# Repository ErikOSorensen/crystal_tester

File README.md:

# Crystal tester
Creating pcbs for crystal tester (for measuring motional parameters for crystal filters).

- 2023-12-17: First G3UUR board populated.
- 2023-12-17: First crystals tested.

## The tester

## First tests

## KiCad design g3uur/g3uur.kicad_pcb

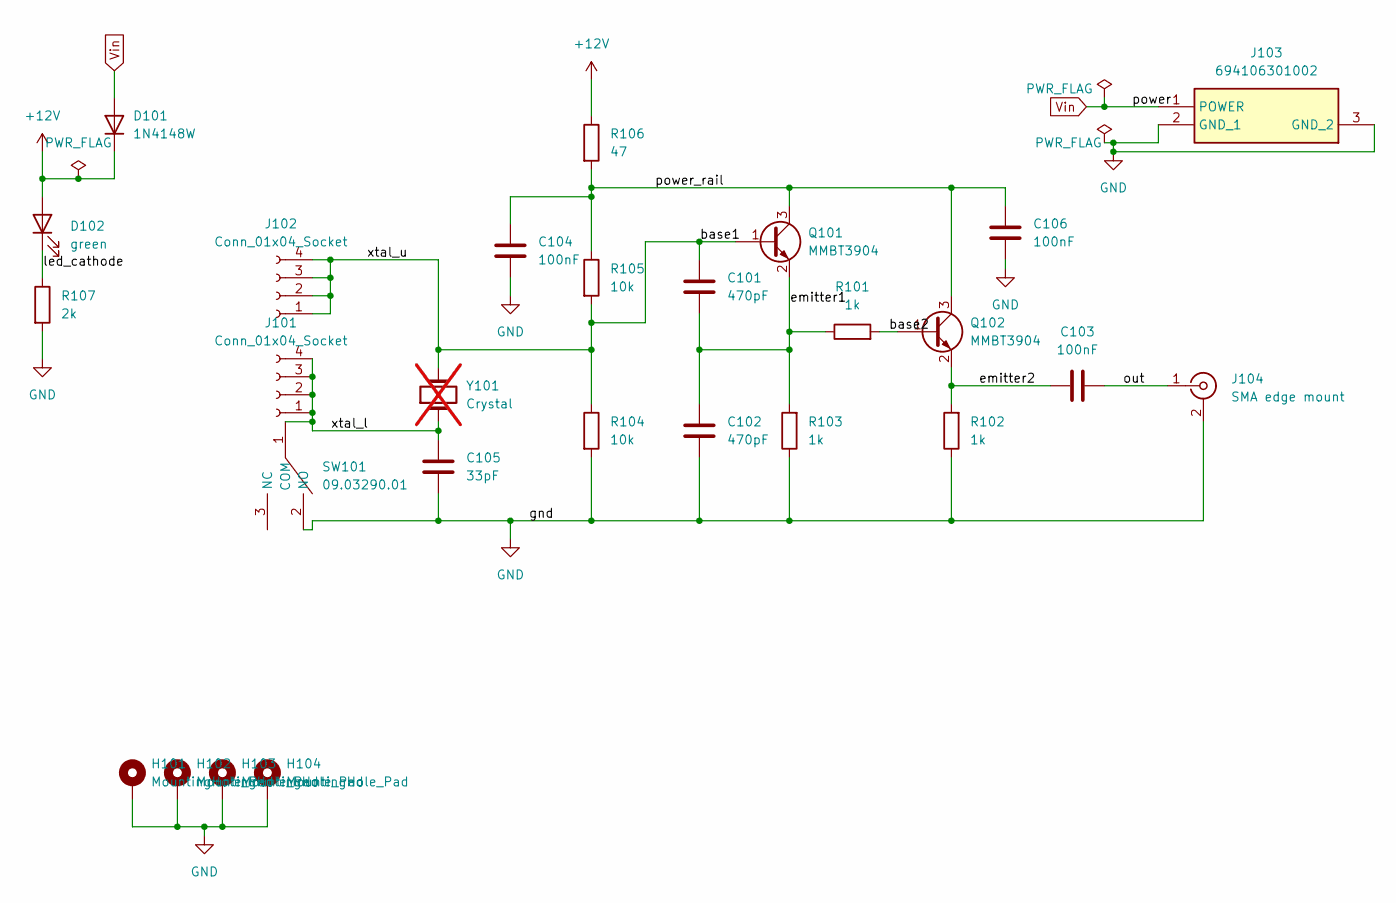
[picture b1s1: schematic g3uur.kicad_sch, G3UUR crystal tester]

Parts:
C101, C102: 470pF; C_0805_2012Metric
C103, C104, C106: 100nF; C_0805_2012Metric
C105: 33pF; C_0805_2012Metric
D101: 1N4148W; D_SOD-123
D102: green; LED_0805_2012Metric_Pad1.15x1.40mm_HandSolder
H101, H102, H103, H104: MountingHole_Pad; MountingHole_3.2mm_M3_DIN965_Pad_TopBottom
J101, J102: Conn_01x04_Socket; PinSocket_1x04_P2.54mm_Vertical
J103: 694106301002; 694106301002_1; Mouser Part Number 710-694106301002
J104: SMA edge mount; SMA_Molex_73251-1153_EdgeMount_Horizontal
Q101, Q102: MMBT3904; SOT-23
R101, R102, R103: 1k; R_0805_2012Metric
R104, R105: 10k; R_0805_2012Metric
R106: 47; R_0805_2012Metric
R107: 2k; R_0805_2012Metric
SW101: 09.03290.01; 090329001; Mouser Part Number 123-09.03290.01
Y101: Crystal; Crystal_SMD_HC49-SD_HandSoldering; not fitted

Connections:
+12V: D101.1 (K), D102.2 (A), R106.1
/base1: C101.1, J102.1, J102.2, J102.3, J102.4, Q101.1 (B), R104.1, R105.2, Y101.2
/base2: Q102.1 (B), R101.2
/emitter1: C101.2, C102.1, Q101.2 (E), R101.1, R103.2
/emitter2: C103.1, Q102.2 (E), R102.2
/led_cathode: D102.1 (K), R107.1
/out: C103.2, J104.1 (In)
/power_rail: C104.1, C106.1, Q101.3 (C), Q102.3 (C), R105.1, R106.2
/xtal_l: C105.1, J101.1, J101.2, J101.3, J101.4, SW101.1 (COM), Y101.1
GND: C102.2, C104.2, C105.2, C106.2, H101.1, H102.1, H103.1, H104.1, J103.2 (GND_1), J103.3 (GND_2), J104.2 (Ext), R102.1, R103.1, R104.2, R107.2, SW101.2 (NO)
Vin: D101.2 (A), J103.1 (POWER)

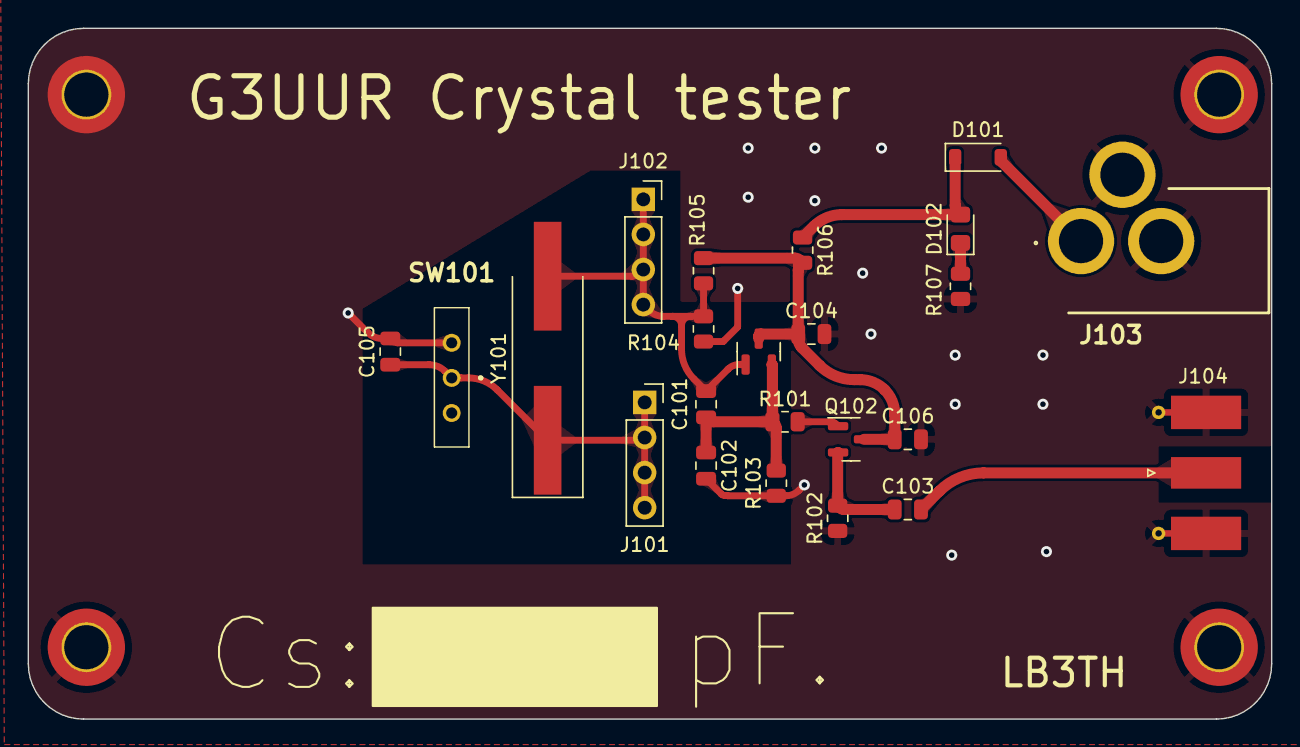
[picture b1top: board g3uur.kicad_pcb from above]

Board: 2 copper layers, 90.0 x 50.0 mm, 27 parts (0 on the bottom side), 11 nets.

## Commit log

2023-12-17 First production attempt.
2023-12-17 Schematic pdf.
2023-12-17 First attempts at testing crystals.
